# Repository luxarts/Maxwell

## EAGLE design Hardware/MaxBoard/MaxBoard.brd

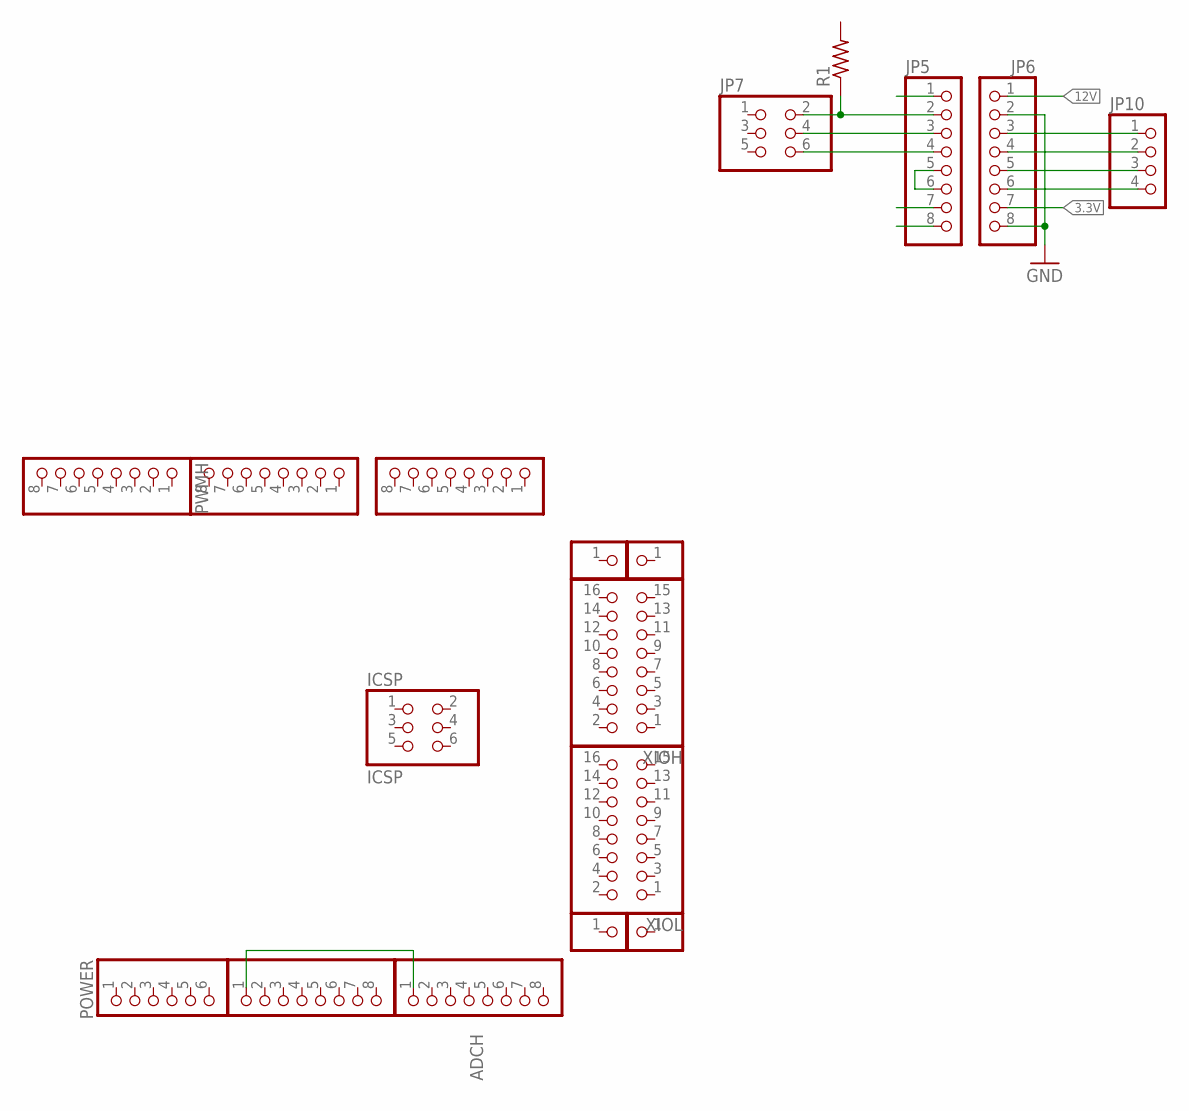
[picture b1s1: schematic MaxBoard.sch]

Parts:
ADCH: PINHD-1X8; 1X08
ADCL: PINHD-1X8; 1X08
COMMUNICATION: PINHD-1X8; 1X08
ICSP: ICSP; 2X03
JP1, JP2, JP3, JP4: PINHD-1X1; 1X01
JP5, JP6: PINHD-1X8; 1X08
JP7: PINHD-2X3; 2X03
JP10: PINHD-1X4; 1X04
POWER: PINHD-1X6; 1X06
PWMH: PINHD-1X8; 1X08
PWML: PINHD-1X8; 1X08
R1: R-US_0207/7; 0207/7
XIOH: PINHD-2X8; 2X08
XIOL: PINHD-2X8; 2X08

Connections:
3.3V: JP6.7
12V: JP6.1
GND: JP6.2, JP6.8
unnamed: ADCH.1, ADCL.1
unnamed: JP5.2, JP7.2, R1.1
unnamed: JP5.3, JP7.4
unnamed: JP5.4, JP7.6
unnamed: JP5.5, JP5.6
unnamed: JP6.3, JP10.1
unnamed: JP6.4, JP10.2
unnamed: JP6.5, JP10.3
unnamed: JP6.6, JP10.4

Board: 2 copper layers, 18 parts (0 on the bottom side), 10 nets, no tracks yet.

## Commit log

2018-03-27 First upload
2018-03-27 WIFI
2018-03-27 Change
2018-03-29 Wifi update
2018-04-05 Fix setOrigin
    Menu option "set origin" didn't work.
2018-04-09 Penholder add
2018-04-09 GUI svg
2018-04-25 update fw
2018-05-11 Added ESP TCP
2018-05-12 Upload
2018-05-15 Websocket test
2018-05-17 Websocket based
2018-05-17 Update web
2018-05-19 Websocket update
2018-05-19 Web update
2018-05-19 Update web
    Control working
    Calibration working
2018-05-19 Exhibition mode
2018-05-26 Board
2018-06-05 minor update
2018-06-06 Temp graphic added
2018-06-08 Penholder model
2018-06-10 Clean
2018-06-13 compress update
2018-06-15 Float Hex converter
    toHex(float)
    toFloat(hex)
    Lectura del archivo eeprom.bin
2018-06-17 AP Fix and eeprom.bin
2018-06-17 SoftAP fix
    Set physical mode to 11G, this fix the unstable state when switching from STA to AP
2018-06-17 Comment
2018-06-20 Fixed upload eeprom
2018-06-20 Fix color for firefox
2018-06-21 Stats implementation
    Added a working script to set/get stats using a json file. Needs to be implemented into the web.
2018-06-25 SD List implementation
    Added a working script to read the files from SD card returned by M20 command. Needs to be implemented into the web.
2018-06-25 Added SD List
2018-06-26 SD list update + features
    - Added showMsg(string): Display a popup message.
    - Added tooltip="message" property for HTML elements to display a message when mouse is over.
    - Added SD control panel (WIP)
2018-06-29 Added alpha radius config
2018-07-11 Fixed wifi + update firmware base
2018-07-19 Added config
2018-07-20 Watchdog disabled (check)
2018-07-25 Updated files
2018-08-07 Compression of web
    - Added gulp installation script (require Node.js)
    - Added gulpfile to compress the web
    - Modified HTML to work with gulpfile
2018-08-07 No changes
2018-08-14 Update models and config
2018-08-27 Update models and fix config file
2018-08-27 Added new version
2018-09-03 Model update
2018-09-04 Update model and added heated bed to config
2018-09-08 Update models
2018-09-10 Added stats calculator (WIP)
    Work in progress
2018-09-10 Added time calc (WIP)
2018-09-11 Update model
2018-09-12 Added stats, fix and some extras
    - Added Maxwell theme
    - Fixed hard-coded colors
    - Server test script (require Python 3)
    Note: Smoosh doesn't work. Fix needed.
2018-09-12 Added bed temp to chart
2018-09-15 Rework web (WIP)
    - Added script to start test server (require python)
    - Added new logo (.png and .ai)
    - Added new web using Materialize
    - Added Sass script to compile Scss (require Sass)
    - Fixed bug in stats.js
2018-09-17 Update icon pack
2018-09-18 Added stats tab
2018-09-21 Web design, fix compress script
2018-09-22 Web update and new gulp task
2018-09-25 Added filament selection in statistics
2018-09-25 Removed unused button and fixed material cost formula
2018-09-28 Update model, added weight in stats web
2018-09-30 Fix energy price in stats
2018-10-02 Control files
2018-10-02 Update effector model
2018-10-10 SD List (need test)
    - File upload (need ack)
    - Delete file
    - Play/pause/stop print
    - Create folder (to do)
    Updated icons
2018-10-11 Added JSON, added M108 and fixes
    - JSON output with M408
    - M108 command to stop printing
    - Fix bug with extruder speed
    - Board fan on Heater 1 pin (D8)
2018-10-13 Fix status on json output, disabled board fan
2018-10-14 Improved eeprom and sd loading, added fwu, json status and added images
2018-10-18 Added calibration page
2018-10-21 Update dimension model
2019-03-09 Changed colors and bugfix
    Delete filament fix
2019-03-18 Added SASS to WEBUI
    Changed theme to blue
2019-03-19 Added control tab
    - Added control tab (WIP)
    - Fix wifi config
